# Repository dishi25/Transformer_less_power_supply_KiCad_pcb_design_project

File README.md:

# Transformer-less Power Supply pcb_design (KiCad Project)

## Overview
This project demonstrates the design of a **transformer-less power supply** using KiCad.  
The circuit converts AC mains input into a regulated DC output using capacitive voltage dropping, rectification, filtering, and regulation.  

---

### Key Components
| Component | Value/Part | Notes |
|-----------|------------|-------|
| R1, R2    | 20kΩ       | Voltage divider |
| R3        | 1MΩ        | Bleeder resistor |
| R4        | 2.2kΩ      | LED current limit |
| C1        | 0.1µF      | Filter capacitor |
| C2        | 1000µF     | Bulk capacitor |
| C3        | 470µF      | Output smoothing |
| D1–D4     | 1N4001     | Bridge rectifier |
| D5, D6    | Zener diodes | Voltage regulation |
| D7        | LED        | Power indicator |
| U1        | LM7805     | 5V regulator |
| J1        | AC input terminal |
| J2        | DC output terminal |

---

## Software
- **EDA Tool:** KiCad 9.0.7  
- **Gerber Viewer:** KiCad Gerber Viewer (or any online Gerber viewer)  
- **Version Control:** Git + GitHub  

---

## Visuals

---

## Safety Disclaimer
This project involves **direct connection to mains AC**.  
It is intended for **educational and simulation purposes only**.  
Do not attempt to build or test without proper isolation, supervision, and protective equipment.  
Always follow electrical safety standards.

---
## Team:
V VAISHNAVI
GURUPRIYAA N
DISHIKA G

## Institution: Vellore Institute of Technology (VIT)

Support If you found this project inspiring, consider giving it a star on GitHub to support further development and encourage open-source innovation.

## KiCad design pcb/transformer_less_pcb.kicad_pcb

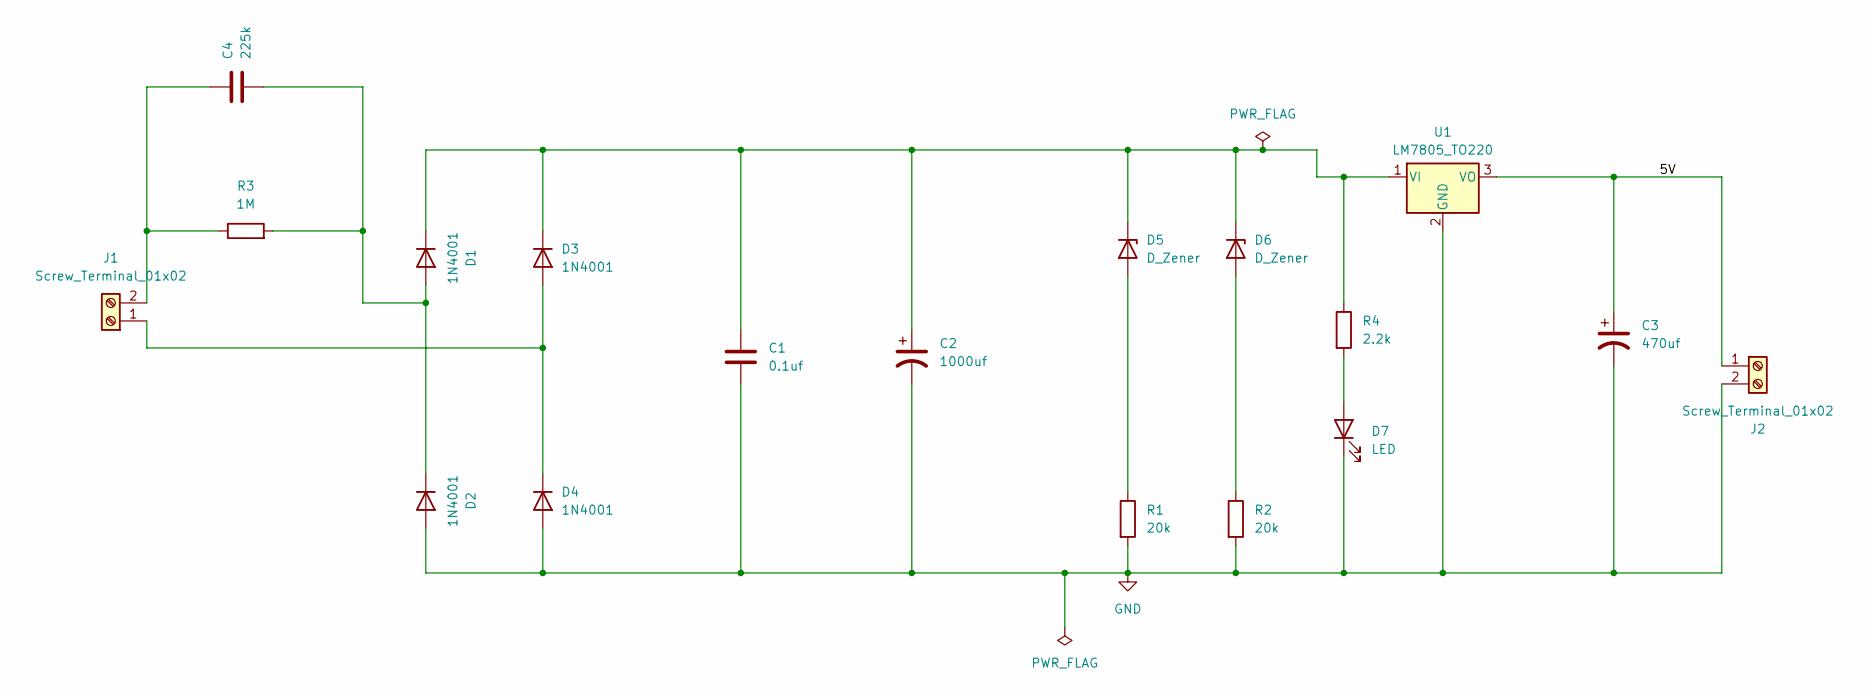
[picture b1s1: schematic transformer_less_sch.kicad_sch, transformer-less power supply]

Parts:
C1: 0.1uf; C_Disc_D4.7mm_W2.5mm_P5.00mm
C2: 1000uf; CP_Radial_D10.0mm_P5.00mm
C3: 470uf; CP_Radial_D10.0mm_P3.80mm
C4: 225k; C_Rect_L18.0mm_W11.0mm_P15.00mm_FKS3_FKP3
D1, D2, D3, D4: 1N4001; D_DO-41_SOD81_P10.16mm_Horizontal
D5, D6: D_Zener; D_A-405_P7.62mm_Horizontal
D7: LED; LED_D5.0mm
J1, J2: Screw_Terminal_01x02; TerminalBlock_MaiXu_MX126-5.0-02P_1x02_P5.00mm
R1, R2: 20k; R_Axial_DIN0207_L6.3mm_D2.5mm_P7.62mm_Horizontal
R3: 1M; R_Axial_DIN0207_L6.3mm_D2.5mm_P7.62mm_Horizontal
R4: 2.2k; R_Axial_DIN0207_L6.3mm_D2.5mm_P7.62mm_Horizontal
U1: LM7805_TO220; TO-220-3_Vertical

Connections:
/5V: C3.1, J2.1, U1.3 (VO)
GND: C1.2, C2.2, C3.2, D2.2 (A), D4.2 (A), D7.1 (K), J2.2, R1.2, R2.2, U1.2 (GND)
unnamed: C4.2, D1.2 (A), D2.1 (K), R3.2
unnamed: C1.1, C2.1, D1.1 (K), D3.1 (K), D5.1 (K), D6.1 (K), R4.1, U1.1 (VI)
unnamed: D3.2 (A), D4.1 (K), J1.1
unnamed: D5.2 (A), R1.1
unnamed: D6.2 (A), R2.1
unnamed: D7.2 (A), R4.2
unnamed: C4.1, J1.2, R3.1

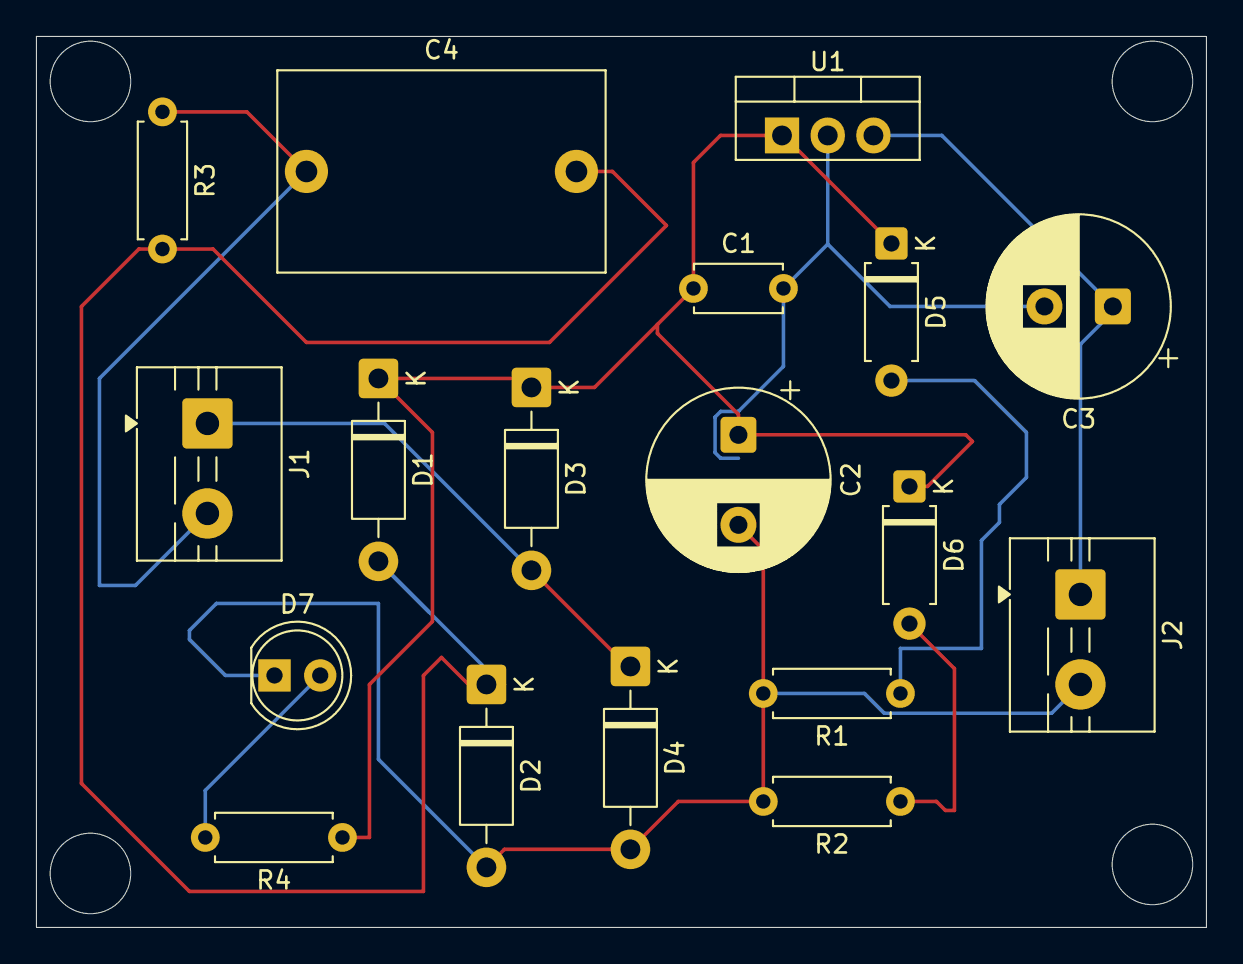
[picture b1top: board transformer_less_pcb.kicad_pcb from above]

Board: 2 copper layers, 65.0 x 49.5 mm, 18 parts (0 on the bottom side), 9 nets.

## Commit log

2026-05-16 Update readme with gerber file information
    Add description for gerber files and KiCad viewer.
2026-05-16 Add description to schematic README
2026-05-16 Add Bill of Materials note to readme
2026-05-16 Revise project title and add team information
    Updated project title and added team and institution details.
